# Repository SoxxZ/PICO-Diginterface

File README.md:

# PICO-Diginterface

An RP2040-based digital interface for amateur radio. Enumerates as a UAC2 sound card and CDC virtual COM port, providing microphone input, PDM speaker output, dual PTT channels, and CAT control passthrough over a single USB connection.

Inspired by [AIOC](https://github.com/skuep/AIOC).

---

## Hardware

The PCB implements full galvanic isolation between the host interface and the radio to eliminate ground loops and RF interference, using PC817 optocouplers and 1:1 600 ohms isolation transformers.

### Pinout

| GPIO | Function       | Direction    | Notes                                                |
|------|----------------|--------------|------------------------------------------------------|
| 4    | UART1 TX       | Output       | Inverted, 4800 baud                                  |
| 5    | UART1 RX       | Input        | Inverted, pull-up enabled                            |
| 12   | PTT Status LED | Output       | Active high; asserted when any PTT channel is active |
| 17   | PDM Data Out   | Output (PIO) | PDM bitstream at 1.536 MHz                           |
| 22   | PTT Channel 1  | Output       | Active high                                          |
| 24   | PTT Channel 2  | Output       | Active high                                          |
| 25   | Board LED      | Output       | Blinks USB status                                    |
| 26   | Mic Input      | Analog input | ADC channel 0, 12-bit, 48 kHz                        |

---

## Firmware

### Overview

When connected to a host PC, the firmware presents three USB interfaces:

- **UAC2 Microphone** — 48 kHz, 16-bit mono audio captured via the on-board 12-bit ADC
- **UAC2 Speaker** — 48 kHz, 16-bit mono audio from the host, output as a PDM bitstream via PIO
- **CDC Serial** — Virtual COM port bridged to UART1 for CAT rig control and radio programming

### Features

- **USB Audio (UAC2)** — Full-duplex USB Audio Class 2 interface. Microphone path: 48 kHz, 12-bit ADC, transmitted as 16-bit PCM. Speaker path: 48 kHz / 16-bit PCM from host, output as a 1.536 MHz PDM bitstream via PIO.
- **Push-to-Talk** — Two independent PTT output channels, keyed automatically when the received audio level exceeds a configurable threshold. A hold-off timer keeps the channel open for a defined period after the signal drops.
- **CAT Control Bridge** — Bidirectional CDC serial passthrough to UART1 (inverted, 4800 baud) for rig control and radio programming.

### LED Status

| Blink Interval | State                   |
|----------------|-------------------------|
| Solid on       | Audio streaming         |
| 250 ms         | Unmounted               |
| 1000 ms        | Mounted, idle           |
| 2500 ms        | Not mounted / suspended |

### Building

#### Prerequisites

- [Raspberry Pi Pico SDK](https://github.com/raspberrypi/pico-sdk) v1.5.1 or later
- CMake 3.19+
- ARM GCC toolchain

#### Compiling

```bash
mkdir build && cd build
cmake .. -DPICO_SDK_PATH=/path/to/pico-sdk
make -j$(nproc)
```

Flash the resulting `.uf2` file by holding BOOTSEL while connecting the board, then copying the file to the mass storage device that appears.

## Enjoy the project and 73 de PP2GS!

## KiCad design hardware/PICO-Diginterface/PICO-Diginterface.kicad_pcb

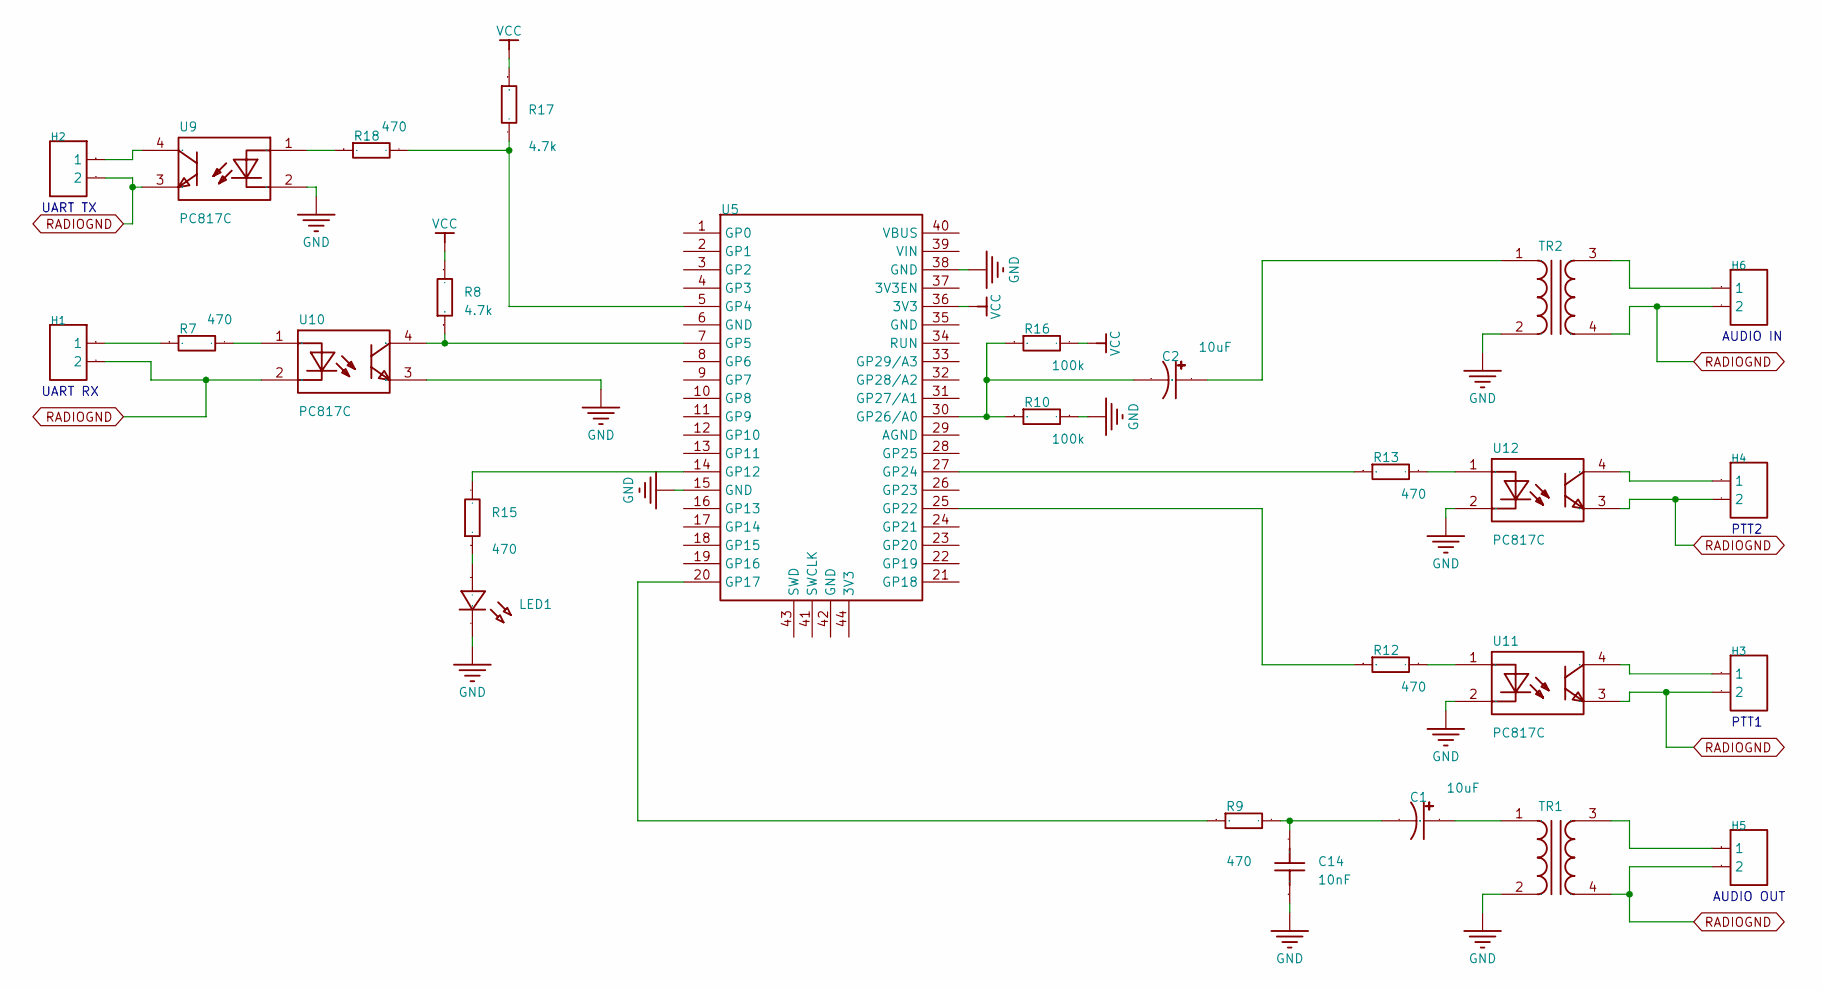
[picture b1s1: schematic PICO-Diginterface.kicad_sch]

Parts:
C1, C2: 10uF; CAP-TH_BD12.5-P5.00-D0.6-FD; Manufacturer Part ECR1EBK222MLL125025; LCSC Part Name 2200uF ±20% 25V
C14: 10nF; CAP-TH_L5.1-W3.2-P2.54-D0.5; Manufacturer Part C322C103K5R5TA; LCSC Part Name 10nF ±10% 50V
H1, H2, H3, H4, H5, H6: HDR-TH_2P-P2.54-V-F
LED1: LED-TH_BD3.0-P2.54-FD
R7, R9, R12, R13, R15, R18: 470; R0603
R8, R17: 4.7k; R0603
R10, R16: 100k; R0603
TR1, TR2: TRANSFORMER AUDIO 1:1; Manufacturer Part AUDIO TRANSFORMER
U5: PurplePICORP2040TH
U9, U10, U11, U12: PC817C; DIP-4_L4.6-W6.5-P2.54-LS7.6-BL; Manufacturer Part PC817C; LCSC Part Name 4引脚DIP封装光电晶体管光电耦合器

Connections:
$1N291: R7.2, U10.1 (AN)
$1N1419: R8.1, U5.7 (GP5), U10.4 (COL)
$1N1678: H1.1, R7.1
$1N2389: H3.1, U11.4 (COL)
$1N2397: R12.2, U11.1 (AN)
$1N2401: R12.1, U5.25 (GP22)
$1N2767: R13.1, U5.27 (GP24)
$1N2874: R13.2, U12.1 (AN)
$1N2953: C2.2, R10.1, R16.1, U5.30 (GP26/A0)
$1N3686: C2.1, TR2.1
$1N3835: H6.1, TR2.3
$1N3910: R15.2, U5.14 (GP12)
$1N3945: LED1.1 (C), R15.1
$1N4712: H2.1, U9.4 (COL)
$1N4720: R18.1, U9.1 (AN)
$1N4725: R17.2, R18.2, U5.5 (GP4)
$1N4836: H4.1, U12.4 (COL)
$1N5390: C1.2, C14.2, R9.2
$1N5395: C1.1, TR1.1
$1N5400: H5.1, TR1.3
$1N5543: R9.1, U5.20 (GP17)
GND: C14.1, LED1.2 (A), R10.2, TR1.2, TR2.2, U5.15 (GND), U5.38 (GND), U9.2 (CAT), U10.3 (EM), U11.2 (CAT), U12.2 (CAT)
RADIOGND: H1.2, H2.2, H3.2, H4.2, H5.2, H6.2, TR1.4, TR2.4, U9.3 (EM), U10.2 (CAT), U11.3 (EM), U12.3 (EM)
VCC: R8.2, R16.2, R17.1, U5.36 (3V3)

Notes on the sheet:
PTT2
PTT1
UART TX
AUDIO IN
AUDIO OUT
UART RX

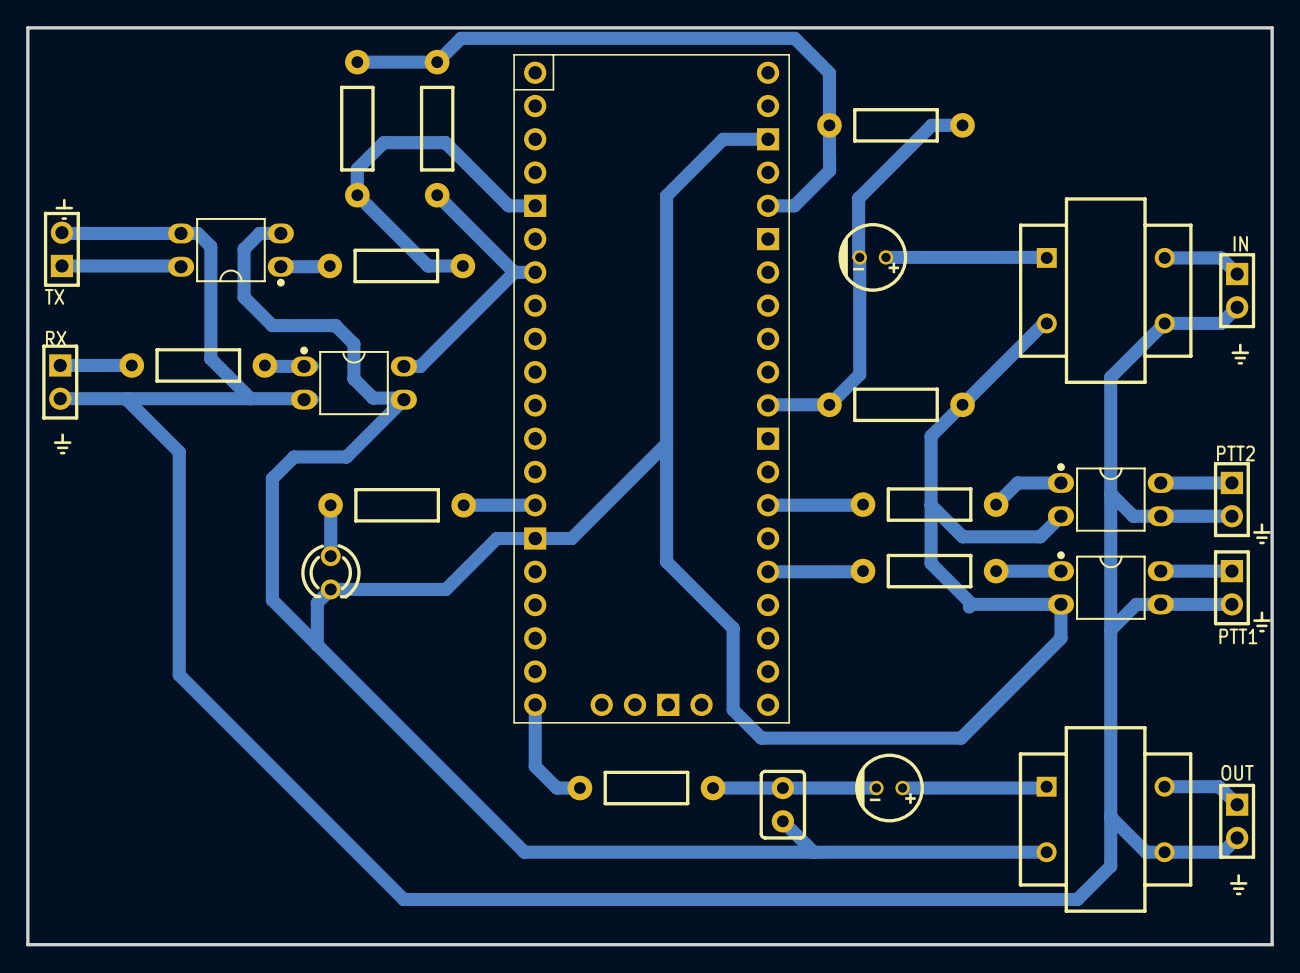
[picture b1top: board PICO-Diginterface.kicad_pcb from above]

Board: 2 copper layers, 95.0 x 70.0 mm, 27 parts (0 on the bottom side), 24 nets.

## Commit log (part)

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2026-05-26 fix CI: bump Pico SDK from 1.5.1 to 2.2.0
    SDK 1.5.1 bundles an old TinyUSB that lacks bsp/board_api.h.
    SDK 2.2.0 has it, matching the local development environment.
2026-05-26 changed from easyeda to kicad
